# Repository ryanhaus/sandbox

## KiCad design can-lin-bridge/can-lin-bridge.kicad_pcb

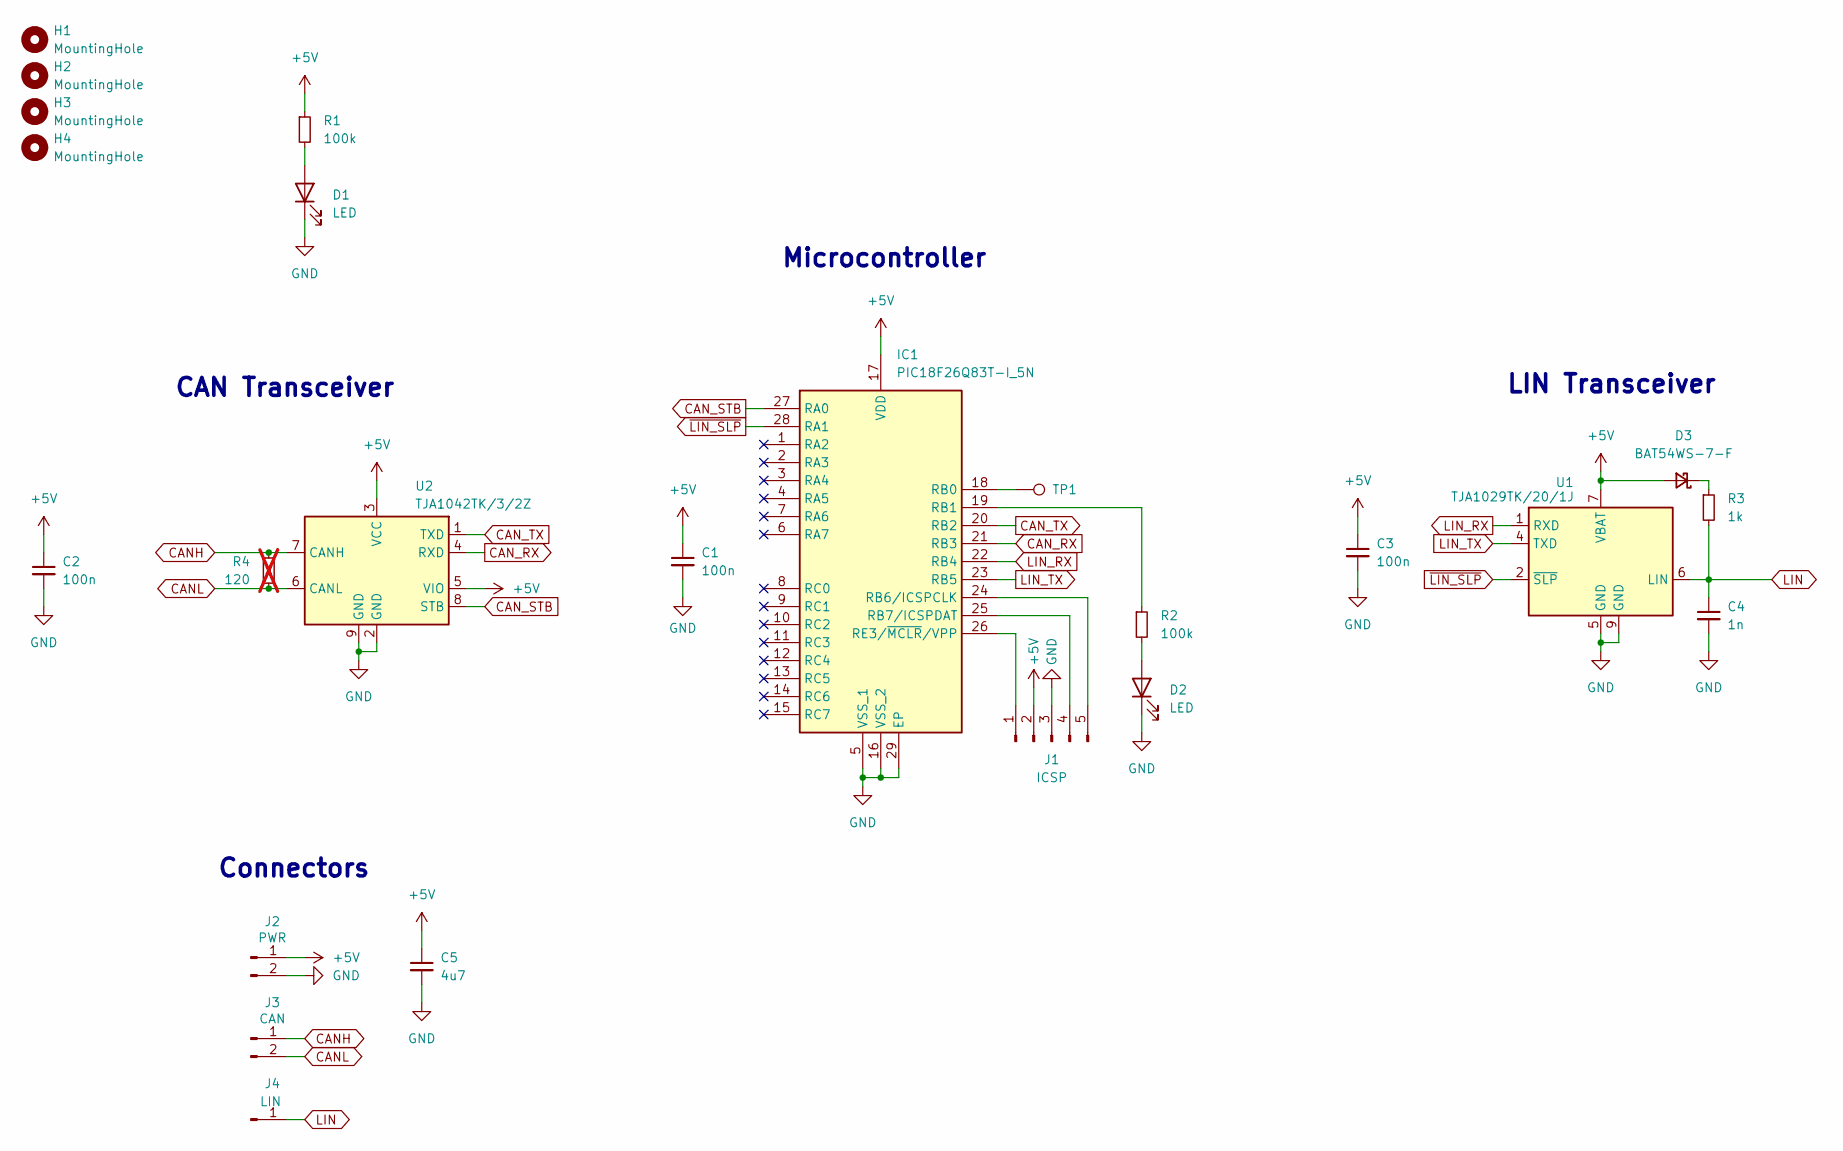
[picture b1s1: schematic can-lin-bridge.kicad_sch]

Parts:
C1, C2, C3: 100n; C_0402_1005Metric
C4: 1n; C_0402_1005Metric
C5: 4u7; C_0603_1608Metric
D1, D2: LED; LED_0402_1005Metric
D3: BAT54WS-7-F; D_SOD-323
H1, H2, H3, H4: MountingHole; MountingHole_2.2mm_M2
IC1: PIC18F26Q83T-I_5N; QFN65P600X600X100-29N-D; Manufacturer_Part_Number PIC18F26Q83T-I/5N; Mouser Part Number 579-PIC18F26Q83TI5N
J1: ICSP; PinHeader_1x05_P1.27mm_Vertical
J2: PWR; PinHeader_1x02_P2.54mm_Vertical
J3: CAN; PinHeader_1x02_P2.54mm_Vertical
J4: LIN; PinHeader_1x01_P2.54mm_Vertical
R1, R2: 100k; R_0402_1005Metric
R3: 1k; R_0402_1005Metric
R4: 120; R_0402_1005Metric; not fitted
TP1: TestPoint; TestPoint_Pad_D1.0mm
U1: TJA1029TK/20/1J; DFN-8-1EP_3x3mm_P0.65mm_EP1.55x2.4mm
U2: TJA1042TK/3/2Z; DFN-8-1EP_3x3mm_P0.65mm_EP1.55x2.4mm

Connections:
+5V: C1.1, C2.1, C3.1, C5.1, D3.2 (A), IC1.17 (VDD), J1.2, J2.1, R1.1, U1.7 (VBAT), U2.3 (VCC), U2.5 (VIO)
CANH: J3.1, R4.1, U2.7 (CANH)
CANL: J3.2, R4.2, U2.6 (CANL)
CAN_RX: IC1.21 (RB3), U2.4 (RXD)
CAN_STB: IC1.27 (RA0), U2.8 (STB)
CAN_TX: IC1.20 (RB2), U2.1 (TXD)
GND: C1.2, C2.2, C3.2, C4.2, C5.2, D1.1 (K), D2.1 (K), IC1.5 (VSS_1), IC1.16 (VSS_2), IC1.29 (EP), J1.3, J2.2, U1.5 (GND), U1.9 (GND), U2.2 (GND), U2.9 (GND)
LIN: C4.1, J4.1, R3.2, U1.6 (LIN)
LIN_RX: IC1.22 (RB4), U1.1 (RXD)
LIN_TX: IC1.23 (RB5), U1.4 (TXD)
unnamed: D1.2 (A), R1.2
unnamed: D2.2 (A), R2.2
unnamed: D3.1 (K), R3.1
unnamed: IC1.18 (RB0), TP1.1
unnamed: IC1.19 (RB1), R2.1
unnamed: IC1.24 (RB6/ICSPCLK), J1.5
unnamed: IC1.25 (RB7/ICSPDAT), J1.4
unnamed: IC1.26 (RE3/~MCLR/VPP), J1.1
~LIN_SLP: IC1.28 (RA1), U1.2 (~SLP)

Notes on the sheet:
LIN Transceiver
CAN Transceiver
Connectors
Microcontroller

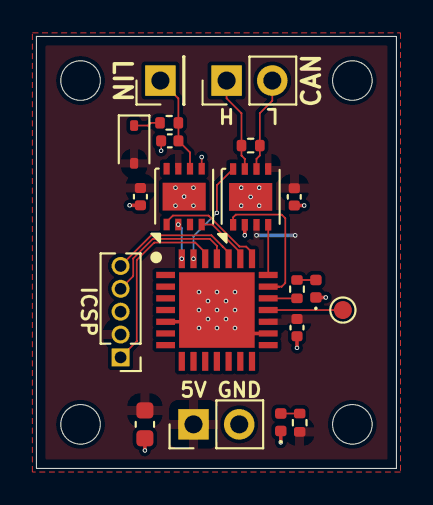
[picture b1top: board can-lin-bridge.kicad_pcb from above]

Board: 2 copper layers, 20.0 x 24.0 mm, 24 parts (0 on the bottom side), 19 nets.

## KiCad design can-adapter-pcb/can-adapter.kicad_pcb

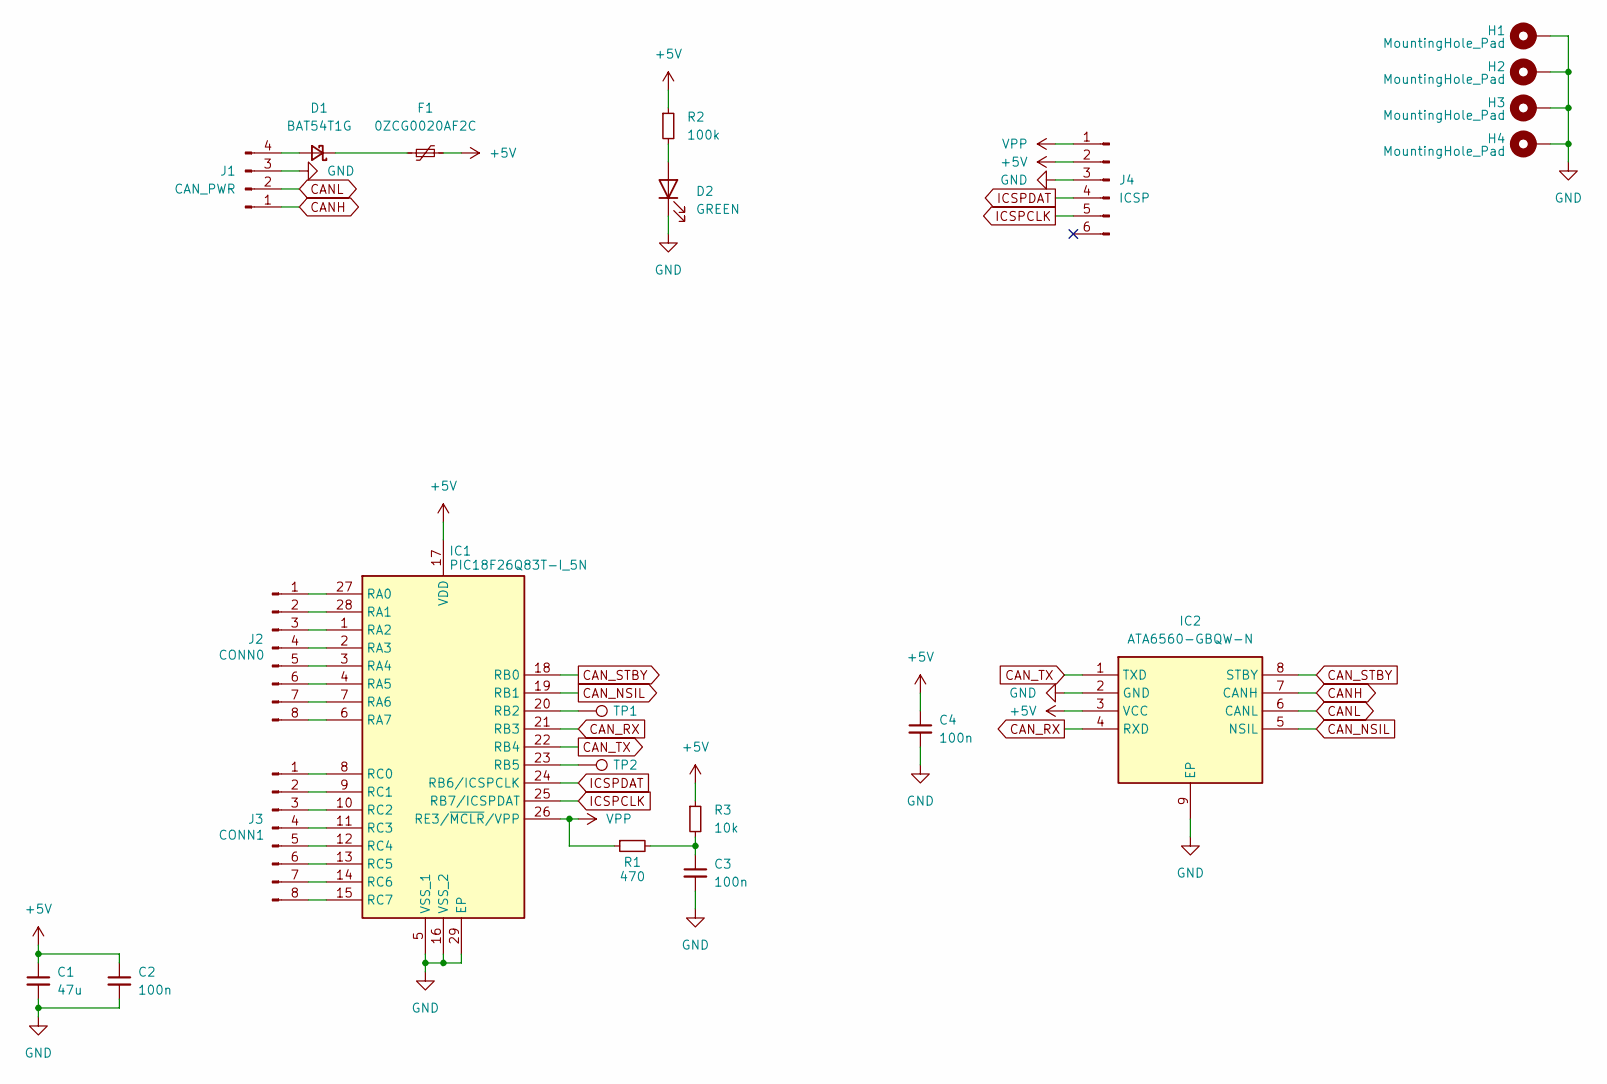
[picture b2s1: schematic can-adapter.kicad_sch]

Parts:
C1: 47u; C_0603_1608Metric
C2, C3, C4: 100n; C_0402_1005Metric
D1: BAT54T1G; D_SOD-123
D2: GREEN; LED_0402_1005Metric
F1: 0ZCG0020AF2C; Fuse_1812_4532Metric
H1, H2, H3, H4: MountingHole_Pad; MountingHole_2.2mm_M2_Pad
IC1: PIC18F26Q83T-I_5N; QFN65P600X600X100-29N-D; Manufacturer_Part_Number PIC18F26Q83T-I/5N; Mouser Part Number 579-PIC18F26Q83TI5N
IC2: ATA6560-GBQW-N; SON65P300X300X90-9N-D; Manufacturer_Part_Number ATA6560-GBQW-N; Mouser Part Number 579-ATA6560-GBQW-N
J1: CAN_PWR; PinHeader_1x04_P2.54mm_Vertical
J2: CONN0; PinHeader_1x08_P1.27mm_Vertical
J3: CONN1; PinHeader_1x08_P1.27mm_Vertical
J4: ICSP; PinHeader_1x06_P2.54mm_Vertical
R1: 470; R_0402_1005Metric
R2: 100k; R_0402_1005Metric
R3: 10k; R_0402_1005Metric
TP1, TP2: TestPoint; TestPoint_Pad_1.0x1.0mm

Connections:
+5V: C1.1, C2.1, C4.1, F1.2, IC1.17 (VDD), IC2.3 (VCC), J4.2, R2.1, R3.1
CANH: IC2.7 (CANH), J1.1
CANL: IC2.6 (CANL), J1.2
CAN_NSIL: IC1.19 (RB1), IC2.5 (NSIL)
CAN_RX: IC1.21 (RB3), IC2.4 (RXD)
CAN_STBY: IC1.18 (RB0), IC2.8 (STBY)
CAN_TX: IC1.22 (RB4), IC2.1 (TXD)
GND: C1.2, C2.2, C3.2, C4.2, D2.1 (K), H1.1, H2.1, H3.1, H4.1, IC1.5 (VSS_1), IC1.16 (VSS_2), IC1.29 (EP), IC2.2 (GND), IC2.9 (EP), J1.3, J4.3
ICSPCLK: IC1.25 (RB7/ICSPDAT), J4.5
ICSPDAT: IC1.24 (RB6/ICSPCLK), J4.4
unnamed: C3.1, R1.2, R3.2
unnamed: D1.2 (A), J1.4
unnamed: D1.1 (K), F1.1
unnamed: D2.2 (A), R2.2
unnamed: IC1.27 (RA0), J2.1
unnamed: IC1.28 (RA1), J2.2
unnamed: IC1.1 (RA2), J2.3
unnamed: IC1.2 (RA3), J2.4
unnamed: IC1.3 (RA4), J2.5
unnamed: IC1.4 (RA5), J2.6
unnamed: IC1.7 (RA6), J2.7
unnamed: IC1.6 (RA7), J2.8
unnamed: IC1.20 (RB2), TP1.1
unnamed: IC1.23 (RB5), TP2.1
unnamed: IC1.8 (RC0), J3.1
unnamed: IC1.9 (RC1), J3.2
unnamed: IC1.10 (RC2), J3.3
unnamed: IC1.11 (RC3), J3.4
unnamed: IC1.12 (RC4), J3.5
unnamed: IC1.13 (RC5), J3.6
unnamed: IC1.14 (RC6), J3.7
unnamed: IC1.15 (RC7), J3.8
VPP: IC1.26 (RE3/~MCLR/VPP), J4.1, R1.1

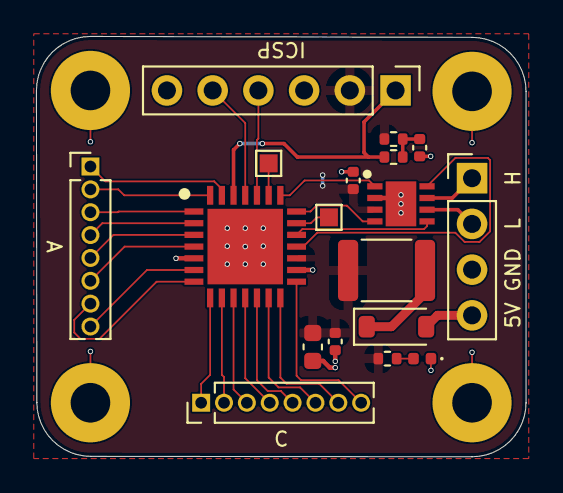
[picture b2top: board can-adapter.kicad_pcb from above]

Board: 2 copper layers, 27.2 x 23.4 mm, 22 parts (0 on the bottom side), 33 nets.

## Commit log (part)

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2025-07-06 ollama-test: add simple test script
2025-07-06 ollama-test: add shebang to main.py
2025-07-06 Ignore .env files
2025-07-06 youtube-song-info: create project
2025-07-06 youtube-song-info: extract video title and description from given video
2025-07-06 youtube-song-info: add missing return for invalid arguments
2025-07-06 youtube-song-info: add comments
2025-07-07 youtube-song-info: add ability to parse automatically generated song videos
2025-07-07 youtube-song-info: download m4a of video for audio fingerprinting
2025-07-07 youtube-song-info: start working with audio fingerprinting
2025-07-17 tca9539-model: Add to repo
2025-07-17 tca9539-model: Add Vivado project file
2025-07-17 tca9539-model: Add IC pins to top-level module
2025-07-17 tca9539-model: Add 'command' enum
2025-07-17 tca9539-model: Add clk pin
2025-07-17 tca9539-model: Define internal registers
2025-07-17 tca9539-model: Make the GPIO output vector a single 16-bit vector
2025-07-17 tca9539-model: Fix syntax errors
2025-07-18 tca9539-model: Separate port 0 and port 1 on GPIO
2025-07-18 tca9539-model: Join register pairs together internally; add comments
2025-07-18 tca9539-model: Add driver for 'port' pins
2025-07-18 tca9539-model: Take polarity_inversion register into account
2025-07-18 tca9539-model: Cleanup, drive reg_input
2025-07-18 tca9539-model: Handle interrupt generation
2025-07-20 can-adapter-pcb: Add to repo
2025-07-20 can-adapter-pcb: Add library for PIC18 microcontroller
2025-07-20 can-adapter-pcb: Clean up schematic symbol for PIC18 microcontroller
2025-07-20 can-adapter-pcb: Add PIC18 microcontroller to schematic with ICSP programming header
2025-07-20 can-adapter-pcb: Add tank and decoupling capacitor
2025-07-20 can-adapter-pcb: Add ATA6560-GBQW-N library (CAN transceiver)
2025-07-20 can-adapter-pcb: Add CAN transceiver to schematic
2025-07-20 can-adapter-pcb: Add connectors for other MCU pins
2025-07-20 can-adapter-pcb: Add recommended auxiliary RC circuit for MCLRn pin on MCU
2025-07-20 can-adapter-pcb: Add power + CAN connector
2025-07-20 can-adapter-pcb: Add power indicator LED
2025-07-20 can-adapter-pcb: Add footprints for all components
2025-07-20 can-adapter-pcb: Use polyfuse instead of regular fuse
2025-07-21 can-adapter-pcb: Create PCB
2025-07-21 can-adapter-pcb: Add annotations to schematic
2025-07-22 can-lin-bridge: Add LIN transceiver (TJA1029)
2025-07-22 can-lin-bridge: Add CAN transceiver (TJA1024)
2025-07-22 can-lin-bridge: Add library for MCU (PIC18F26Q83T-I5N)
2025-07-22 can-lin-bridge: Add MCU to schematic (no connections yet)
2025-07-22 tca9539-model: Change I2C pins
2025-07-22 tca9539-model: Add resources to project
2025-07-22 tca9539-model: Add I2C slave
2025-07-23 tca9539-model: Move around i2cslave core files
2025-07-23 tca9539-model: Rename i2cslave core files to be specific to TCA9539 project
2025-07-23 tca9539-model: Further modify i2cSlave to have module names specific to TCA9539; add dynamic I2C addressing
2025-07-23 tca9539-model: Modify I2C slave & register interface to match that of the TCA9539
2025-07-23 tca9539-model: Make sure internal registers get reset to the correct values
2025-07-24 tca9539-model: Rename 'port' to 'io_port'
2025-07-24 tca9539-model: Remove interrupt logic, change io_port to not use inout
2025-07-24 tca9539-model: Further update TCA9539 module to not use inouts
2025-07-25 tca9539-model: Fix issues with tca9539 module
2025-07-25 tca9539-model: Clean up naming and clarify active low enables
2025-07-25 tca9539-model: Fix I2C device address to be 7 bits instead of 8
2025-07-29 fan-board-interface: Completely abstract I2C methods by abstracting flags to not be specific to Aardvark
2025-07-29 tca9539-model: Rearrange for clarity
2025-07-29 tca9539-model: Fix register conversions
2025-07-29 kernel-modules: Gracefully handle writes of >64 bytes by ignoring any further bytes
2025-07-29 kernel-modules: Add to repo with 'hello' kernel module and Makefile
2025-07-29 kernel-modules: Get basic character device reading to work
2025-07-29 can-lin-bridge: Add power indicator and status LEDs
2025-07-29 can-lin-bridge: Add ICSP programmer header
2025-07-29 vivado-pullup-test: fix to drive output either high-impedance or as 0
2025-07-29 updi-phy-test: add constraints & top-level module
2025-07-29 can-lin-bridge: Add labels to schematic
2025-07-29 vivado-pullup-test: add to repo
2025-07-29 fan-board-interface: add missing return statement
2025-07-29 can-lin-bridge: Connect CAN and LIN transceivers to the microcontroller
2025-07-29 tca9539-model: Fix I2C communication error
2025-07-29 kernel-modules: Get writing to work with basic character device
2025-07-29 can-lin-bridge: Add decoupling capacitors for all ICs
2025-07-29 updi-phy-test: add to repo w/ updi-fpga submodule
2025-07-29 updi-phy-test: update updi-fpga submodule & configure to use fifo's 'almost_full' instead of 'full'
2025-07-29 kernel-modules: Remove debug print statements from 'device_write'
2025-07-30 fan-board-interface: Remove print statement from AT24C128 controller
2025-07-31 kernel-modules: Add 'addition' kernel module
2025-07-31 kernel-modules: Fix issue in 'addition' module that prevented it from printing out anything for a sum value of 0
2025-08-01 i2c-eeprom-sim: Add to repo with 'verilog-i2c' core
2025-08-01 fan-board-interface: Remove from repo
2025-08-01 i2c-eeprom-sim: Start writing at24c02 module
2025-08-01 i2c-eeprom-sim: Move all signals to top of module
2025-08-01 i2c-eeprom-sim: Start writing at24c02_ctl module (untested)
2025-08-02 can-lin-bridge: Add footprints to all components
2025-08-02 can-lin-bridge: Add in auxiliary components for LIN bus
2025-08-03 can-lin-bridge: Add CAN bus, LIN bus, and power connectors to schematic
2025-08-03 can-lin-bridge: Add optional 120 Ohm resistor to CAN bus lines
2025-08-03 can-lin-bridge: Connect LIN sleep and CAN standby pins to microcontroller
2025-08-03 can-lin-bridge: Add 4.7 uF tank capacitor
2025-08-03 can-lin-bridge: Route out PCB
2025-08-03 fpga-video-sim: Add to repo with empty top module & simulation program
2025-08-03 fpga-video-sim: Add video_timing_gen module, which generates timing signals for parallel video output
2025-08-03 fpga-video-sim: Modify video_timing_gen module to output the position in the display instead of the counter values, as well as a signal indicating if current pos is in display region
2025-08-03 fpga-video-sim: Update top-level module to use video_timing_gen module and generate some basic video
2025-08-03 fpga-video-sim: Fix systemverilog syntax errors
2025-08-03 fpga-video-sim: Start updating simulation program to use marlin for hardware simulation
2025-08-03 fpga-video-sim: Begin writing tests using marlin
2025-08-04 fpga-video-sim: Finish simulation program to show video output
2025-08-04 fpga-video-sim: Start to clean up tests format and add actual tests
2025-08-04 i2c-eeprom-sim: Add tb, get working up to the point of sending an address to EEPROM over I2C
2025-08-04 i2c-eeprom-sim: Get write transfers working
2025-08-04 i2c-eeprom-sim: Get EEPROM reads working
2025-08-04 i2c-eeprom-sim: Improve test
2025-08-04 i2c-eeprom-sim: Formatting
2025-08-04 i2c-eeprom-sim: Add comments to top of modules
2025-08-05 fpga-video-sim: Add test for HSYNC period
2025-08-05 fpga-video-sim: Add test for VSYNC period
2025-08-05 i2c-eeprom-sim: Add delay before waiting for ctl_module_ready to go high in testbench
2025-08-05 i2c-eeprom-sim: Add disclaimer about I2C bus errors
2025-08-05 i2c-eeprom-sim: Clean up modules and functionality, add single byte test, get single byte writes and reads working, note a TODO fix
2025-08-06 i2c-eeprom-sim: Fix issues with reading
2025-08-06 i2c-eeprom-sim: Clean up modules & add more comments
2025-08-06 i2c-eeprom-sim: Do multiple single-byte reads
2025-08-06 i2c-eeprom-sim: Add state to controller to wait for write to finish completely before idling
2025-08-08 fpga-video-sim: Add test using cocotb (python)
2025-08-24 lvgl: Add to repos along with lvgl submodule
2025-08-24 zephyr/blinky: Add to repo
2025-08-24 zephyr/threads: Add to repo
2025-08-24 zephyr/lvgl: Add to repo with empty window
2025-08-24 zephyr/lvgl: Add simple label to app
2025-08-24 zephyr/lvgl-threads: Add to repo (copied from zephyr/lvgl)
2025-08-25 zephyr/threads-share: Add to repo with simple 'volatile' to share value between threads
2025-09-02 zephyr/threads-share: Move 'volatile' test to its own file
2025-09-02 zephyr/threads-share: Add atomic test
2025-09-02 zephyr/threads-share: Add mutex test
2025-09-03 zephyr/lvgl-threads: Add to repo with simple text output with sensor value
2025-09-03 zephyr/lvgl-threads: Add indicator line for sensor value
2025-09-03 zephyr: Move all apps to new 'apps' directory
2025-09-03 zephyr/lvgl-threads: Change screen size to match STM32 board (480x272)
2025-09-03 zephyr/lvgl-threads: Fix compiler warnings about implicit float/double conversions
2025-09-04 zephyr/lvgl-threads: Begin switching over to using a LVGL scale (although right now the indicator is broken)
2025-09-04 lvgl: Remove from repo
2025-09-05 zephyr/lvgl-threads: Rename native_sim/native/64 overlay file so that it is automatically recognized by west
2025-09-05 zephyr/lvgl-threads: Center line and scale; do not call lv_timer_handler() before main loop
2025-09-05 zephyr/lvgl-threads: Go back to explicitly setting line position to avoid bug with LVGL
2025-09-07 zephyr/lvgl-threads: Begin writing in devicetree support for display on STM32H735G_DISCO board
2025-09-08 zephyr/lvgl-threads: Get everything to fit into memory keeping 16KB memory pool for LVGL
2025-09-08 zephyr/lvgl-threads: Enable *printf floating point support, add print statement on sensor value update for debugging
2025-09-08 zephyr/lvgl-threads: Enable shell usage
2025-09-08 zephyr/lvgl-threads: Add pins to devicetree for stm32 display controller
2025-09-08 zephyr/lvgl-threads: For stm32 target, modify LVGL memory pool size and move it over to SRAM1 bank to free up RAM space
2025-09-08 zephyr/lvgl-threads: Remove unused variables
2025-09-08 zephyr/lvgl-threads: Increase LVGL VDB size; move it to the DTCM memory region
2025-09-08 zephyr/lvgl-threads: Optimize LVGL flash usage, modify fonts and sizes
2025-09-09 zephyr/lvgl-threads: Fix return statement in blinky function
2025-09-09 zephyr/lvgl-threads: Temporarily use dummy display for stm32 target and change LVGL memory sizes & move back to main RAM
2025-09-09 zephyr/lvgl-threads: Set up clocks needed to drive LTDC peripheral
2025-09-09 zephyr/lvgl-threads: Get LTDC peripheral WORKING with LVGL
2025-09-09 zephyr/lvgl-threads: Move things around in memory to free up some space in main system RAM region
2025-09-09 zephyr/lvgl-threads: Remove lvgl.def-back-color-red from devicetree
2025-09-09 zephyr/lvgl-threads: Remove blinky thread
2025-09-09 zephyr/lvgl-threads: Go back to using custom scale line function, however no longer statically declare 'line_pts' to allow for multiple lines
2025-09-09 zephyr/lvgl-threads: Dynamically allocate line_pts for a line in 'update_scale_line_val'
2025-09-10 zephyr/lvgl-threads: Move the label into the scale
2025-09-10 zephyr/lvgl-threads: Change label font size, update text in 'update_scale_custom' method
2025-09-10 zephyr/lvgl-threads: Add 'setup_scale_custom' method to make creating multiple scales easier
2025-09-10 zephyr/lvgl-threads: Move custom_scale to its own header/C files
2025-09-10 zephyr/lvgl-threads: Set up the screen as a grid, with the currently existing scale centered in the left half.
2025-09-10 zephyr/lvgl-threads: Add second scale to right side of grid
2025-09-13 zephyr/lvgl-threads: Only sleep for LVGL thread manager for as little as needed for performance
2025-09-15 zephyr/canbus: Add to repo with simple tick function (no CAN functionality yet)
2025-09-15 zephyr/canbus: Implement CANbus test
2025-12-12 minesweeper: Add to repo with basic printing of minefield
2026-02-24 aes-encryption: Get simple encryption working
2026-02-24 aes-encryption: Allow multiple blocks to be encrypted at once
2026-04-28 sdl: Add to repo
2026-04-29 sdl: Move fetching dependencies to separate file
2026-04-29 sdl: Add audio
2026-04-30 sdl: Add ImPlot experiments
2026-04-30 sdl: Add README
2026-04-30 sdl: Formatting
2026-04-30 sdl: Fix executable name
